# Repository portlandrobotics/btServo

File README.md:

btServo
=======

PARTS hobby servo controller project

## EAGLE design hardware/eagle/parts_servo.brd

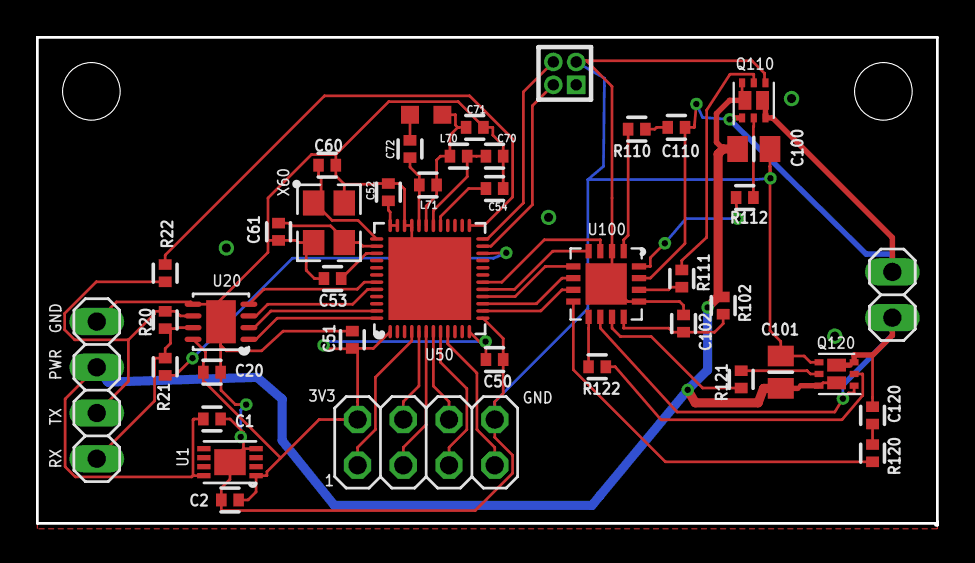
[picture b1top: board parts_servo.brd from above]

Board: 2 copper layers, 50.0 x 27.1 mm, 43 parts (0 on the bottom side), 48 nets.

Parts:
C1, C2, C102, C110, C120: 1; 0402-B
C20, C50, C51, C53: 0.1; 0402-B
C52: .001; 0402-B
C54: .047; 0402-B
C60, C61: 8pF; 0402-B
C70: .0022; 0402-B
C71: np; 0402-B
C72: 2.2pF; 0402-B
C100, C101: 10; 0805-B
JP1: I/O; 1X04
JP2: Sensor; 2X04
JP3: Motor; 1X02
JP4: SWD; PINHEADER-2X2-0.05_IN
L70: 10nH; 0402-B
L71: 4.7nH; 0402-B
Q110, Q120: PMDPB28UN; DFN-6(2X2)+2EP(TRANSISTOR)
R20: 120(np); 0402-B
R21, R22: 4.7k(np); 0402-B
R102, R112, R122: 2.2; 0402-B
R110, R120: 1; 0402-B
R111, R121: 0; 0402-B
TP1: ANT1; TESTPOINT-(1X1)CREAMED
TP2: ANT_FEED; TESTPOINT-(1X1)CREAMED
U1: MCP1703-3302; DFN-8(2X3)+EP
U20: sn65hvd72; DFN-8(3X3)+EP
U50: nRF51822; DFN-48(6X6)+EP
U100: RT9625A; QFN-16(4X4)+EP
X60: CX3225GB16000P0HPQCC; CRYSTAL-3.2X2.5(4_TERMINAL)

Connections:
3.3V: C2.1, C20.1, C50.1, C51.1, JP2.2, U1.1, U20.8, U50.1, U50.12
ANT1: C71.1, L70.1, L71.2, TP1.TP, U50.31
ANT2: C72.1, L71.1, U50.32
ANT_FEED: C72.2, TP2.TP
AVDD: C52.1, U50.35, U50.36
BOOT1: R120.1, U100.8
BOOT1_SNUB: C120.1, R120.2
BOOT1_SNUB1: C110.1, R110.2
BOOT2: R110.1, U100.1
D1/TX: JP1.3, R20.2, R22.1, U20.6
D2/RX: JP1.4, R20.1, R21.1, U20.7
DEC1: C53.1, U50.39
DEC2: C54.1, U50.29
DIFFERENTIAL_INPUT: U20.1, U50.48
DIFFERENTIAL_INPUT_EN: U20.2, U50.47
DIFFERENTIAL_OUTPUT: U20.4, U50.43
DIFFERENTIAL_OUTPUT_EN: U20.3, U50.44
GND: C1.2, C2.2, C20.2, C50.2, C51.2, C52.2, C53.2, C54.2, C60.2, C61.2, C70.2, C71.2, C100.2, C101.2, C102.2, JP1.1, JP2.8, JP4.3, Q110.4, Q120.4, U1.4, U1.PAD, U20.5, U20.PAD, U50.13, U50.33, U50.34, U50.PAD, U100.2, U100.13, U100.PAD, X60.2, X60.4
HSCLK_IN: C60.1, U50.37, X60.1
HSCLK_OUT: C61.1, U50.38, X60.3
LGATE1: R121.1, U100.11
LGATE2: R111.1, U100.14
MOTOR1: C120.2, JP3.1, Q120.1, Q120.3, Q120.P8, U100.10
MOTOR2: C110.2, JP3.2, Q110.1, Q110.3, Q110.P8, U100.15
POWER_IN: C1.1, C100.1, C101.1, JP1.2, Q110.6, Q110.P7, Q120.6, Q120.P7, R102.2, U1.8
PWM1: U50.15, U100.6
PWM1_EN: U50.16, U100.5
PWM2: U50.18, U100.3
PWM2_EN: U50.17, U100.4
PWM_POR: U50.14, U100.7
PWM_VCC: C102.1, R102.1, U100.12
QLGATE1: Q120.5, R121.2
QLGATE2: Q110.5, R111.2
QUGATE1: Q120.2, R122.2
QUGATE2: Q110.2, R112.2
SENSOR1: JP2.1, U50.4
SENSOR2: JP2.3, U50.6
SENSOR3: JP2.4, U50.5
SENSOR4: JP2.5, U50.8
SENSOR5: JP2.6, U50.7
SENSOR6: JP2.7, U50.9
SWDCLK: JP4.4, U50.24
SWDIO: JP4.2, U50.23
UGATE1: R122.1, U100.9
UGATE2: R112.1, U100.16
UNIPOLAR_INPUT: R21.2, U50.22
UNIPOLAR_OUTPUT: R22.2, U50.25
VDD_PA: C70.1, L70.2, U50.30

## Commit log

2014-04-14 Initial prototype design by Tim
2014-04-15 Add pinswaps to nRF
2014-04-15 Initial layout
2014-04-15 Removed all the DRC errors.
2014-04-15 resize vias for LPKF
2014-04-15 Fix DRC errors from via resize
2014-04-15 Fatten some traces, fix DRC and routing
2014-04-15 Move programming header to edge of board
2014-04-16 Connect the center pad on the QFN48 to GND.
2014-04-16 Connect NRF center pad to GND. Add ground pour on bottom of board to improve current return from motor FETs.
2014-04-16 Clean up silkscreen text
2014-04-16 Set bottom fill to net GND. Added mounting holes and a few extra GND vias.
2014-05-07 Initial firmware test based on Nordic pwm code
2014-05-13 Added ADC read code, and a basic PWM function. Replaced main loop to call them.
2014-06-10 First pass at BLE radio control of servo. Very crude proportional control based on potentiometer feedback. Radio code based on Nordic BLE based UART example.
2014-07-24 Disable timeout by switching to general discovery mode. Implement new communication protocol and register map.
2014-07-24 Make register address 16 bits.
2014-09-08 Second rev of board design. Shrink to servo case size
2014-09-10 Update pin mapping for new board and SPI commands for the AS5050. Doesn't seem to work though.
2014-09-12 Wrote some AS5050 code to reset the chip on boot and if it reports an error. This is all untested, since I don't have a working part at the moment.
2014-09-12 Fix factor of 4 error in position reading.
2014-09-12 fix bitmask typo
2015-01-05 Add first version of KiCAD hardware files
2015-01-14 Fix incorrect connections on AS5050
2015-03-17 New board layout. Version sent to DirtyPCBs for thinner boards
2015-04-11 Initial commit of prototype android app.
2015-04-21 Rev protocol to add command to response message. Add target arrow to wheel display. Add motor switch.
2015-04-21 Rev protocol to add command to response. Add OFF mode.
2015-05-14 correct motor direction control (reverse it)
2015-05-14 board layout cleanup
2015-08-31 Add pi filter to matching network. Clean up routing and create parts_servo2.kicad_pcb with latest changes
2015-09-15 new board layout: parts_servo3.kicad_pcb
2016-06-07 Update PCB
2016-06-07 Update firmware to use nRF51 V9 SDK with standard GCC Makefile and Eclipse project
